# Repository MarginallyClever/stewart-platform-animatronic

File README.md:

# stewart-platform-animatronic

https://www.instagram.com/p/BleN0-bjPU8/

These are the printed parts, PCB design files, and laser cutting plans for miniature stewart platforms used in animatronics.

There are four in the instagram link above.  To make ONE of these platforms you will need

6x M3 rod 10cm long
12x M3x10 screws (can be M3x15)
18x M3x15 screws
3x 3d printed lower gimbal limit
6x 3d printed servo horn 
6x 3d printed servo mount
1x 3d printed top
1x laser cut floor A
1x laser cut floor B

For the handle you'll need 3x M3x15 screws.

To fit the servo into the servo mount I unscrewed the back so the wire would bend down and out of the way.  This is convenient on the input side where I also removed one gear AND unsoldered the white wire and resoldered it to the potentiometer.

The potentiometer returns a value between ~110 and ~520 (of a possible 0-1023).  In the code I adjusted the floor and ceiling values to get the full range of motion out of the servos.

To attach the arms to the input servos, I opened the serial window and turned the servo until it was in middle position, then attached the arm horizontally.  The output servos could then be attached to match.  If there's a better way to do this, please let me know.

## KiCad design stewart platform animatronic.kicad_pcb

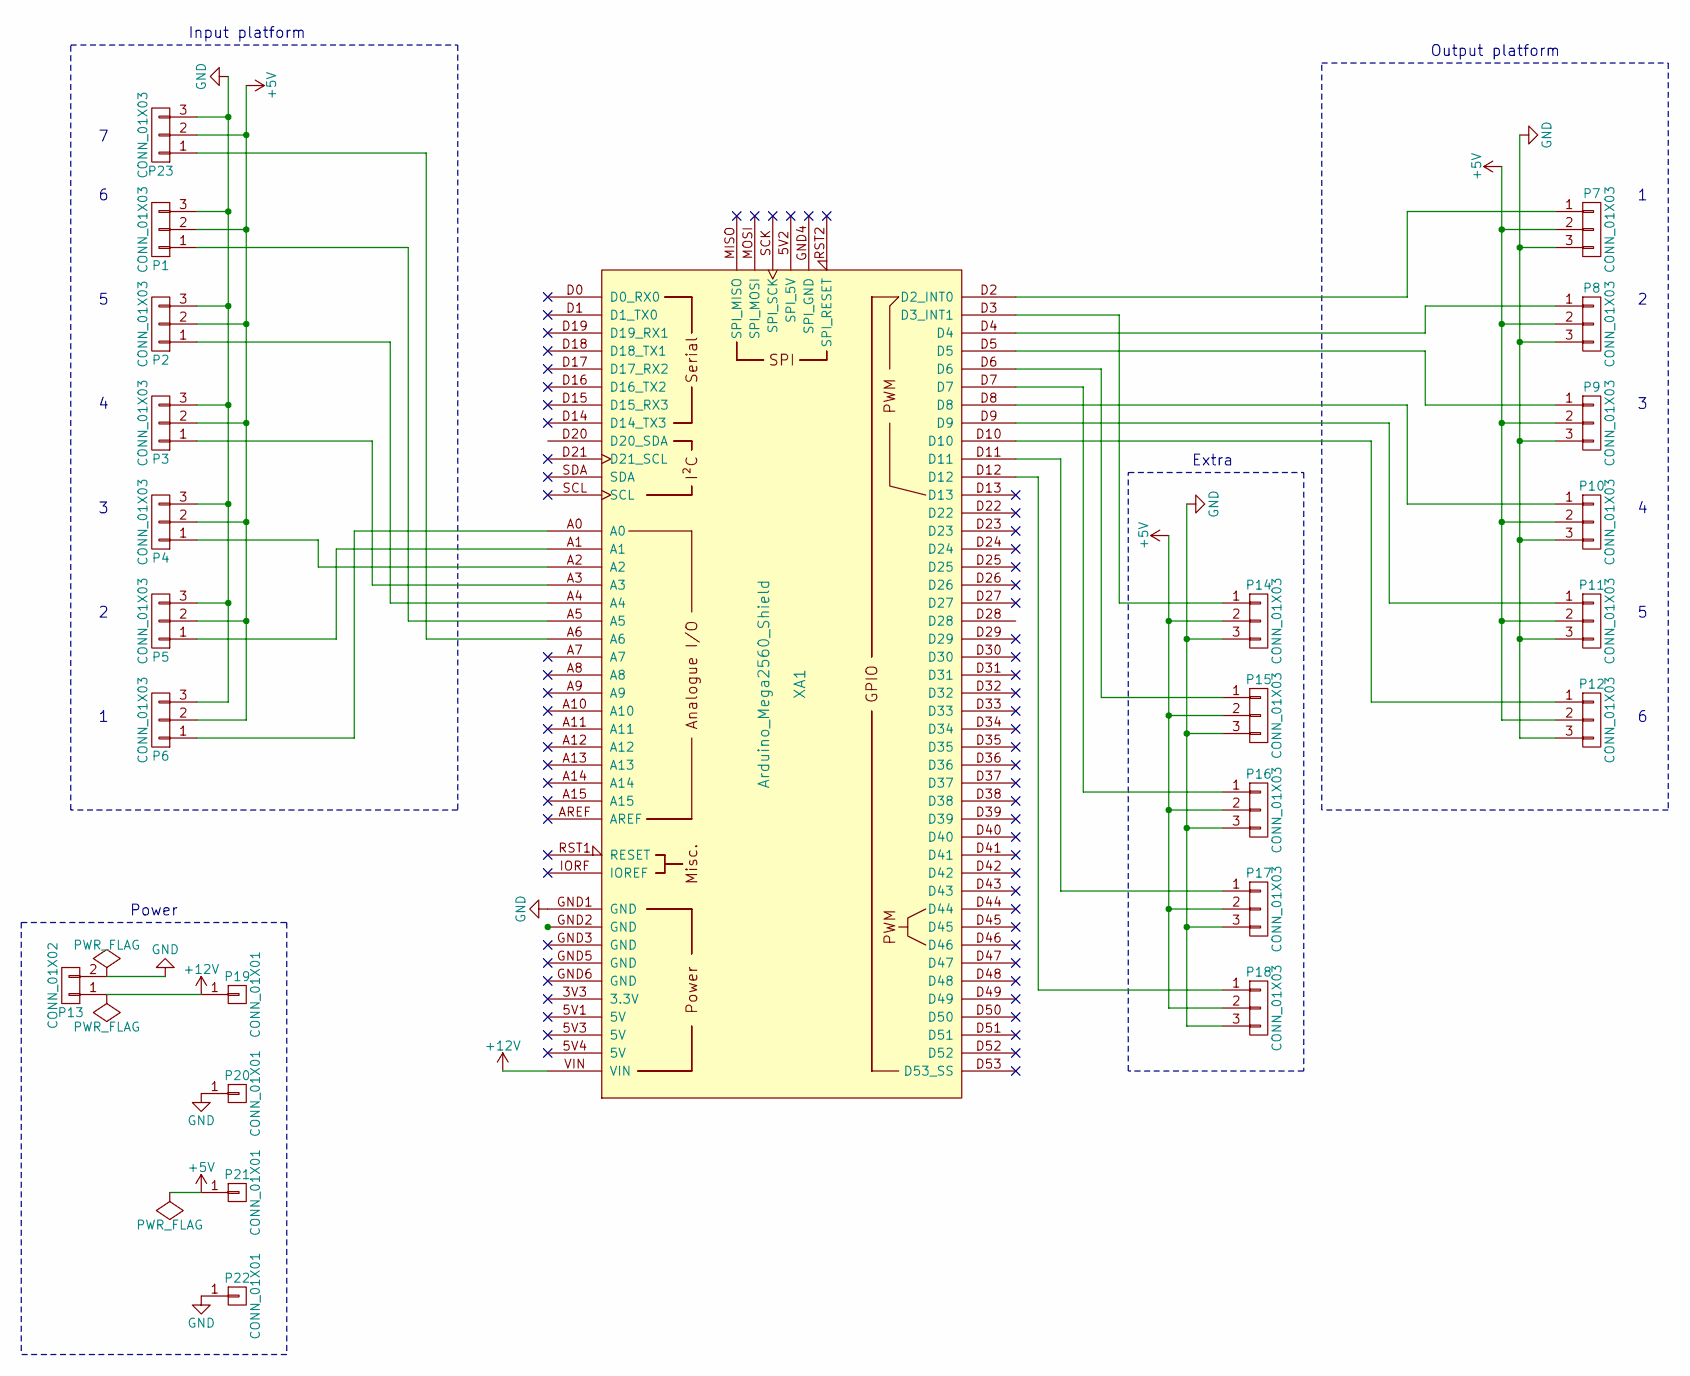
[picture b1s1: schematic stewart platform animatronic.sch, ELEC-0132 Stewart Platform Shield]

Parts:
P1, P2, P3, P4, P5, P6, P7, P8, P9, P10, P11, P12, P14, P15, P16, P17, P18, P23: CONN_01X03; Socket_Strip_Straight_1x03_Pitch2.54mm
P13: CONN_01X02; TerminalBlock_bornier-2_P5.08mm
P19, P20, P21, P22: CONN_01X01; Socket_Strip_Straight_1x01_Pitch2.54mm
XA1: Arduino_Mega2560_Shield

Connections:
+5V: P1.2, P2.2, P3.2, P4.2, P5.2, P6.2, P7.2, P8.2, P9.2, P10.2, P11.2, P12.2, P14.2, P15.2, P16.2, P17.2, P18.2, P21.1, P23.2
+12V: P13.1, P19.1, XA1.VIN
GND: P1.3, P2.3, P3.3, P4.3, P5.3, P6.3, P7.3, P8.3, P9.3, P10.3, P11.3, P12.3, P13.2, P14.3, P15.3, P16.3, P17.3, P18.3, P20.1, P22.1, P23.3, XA1.GND1 (GND)
unnamed: P1.1, XA1.A5
unnamed: P2.1, XA1.A4
unnamed: P3.1, XA1.A3
unnamed: P4.1, XA1.A2
unnamed: P5.1, XA1.A1
unnamed: P6.1, XA1.A0
unnamed: P7.1, XA1.D2 (D2_INT0)
unnamed: P8.1, XA1.D4
unnamed: P9.1, XA1.D5
unnamed: P10.1, XA1.D8
unnamed: P11.1, XA1.D9
unnamed: P12.1, XA1.D10
unnamed: P14.1, XA1.D3 (D3_INT1)
unnamed: P15.1, XA1.D6
unnamed: P16.1, XA1.D7
unnamed: P17.1, XA1.D11
unnamed: P18.1, XA1.D12
unnamed: P23.1, XA1.A6

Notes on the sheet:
Input platform
Output platform
Power
Extra
1 2 3 4 5 6
6 5 4 3 2 1

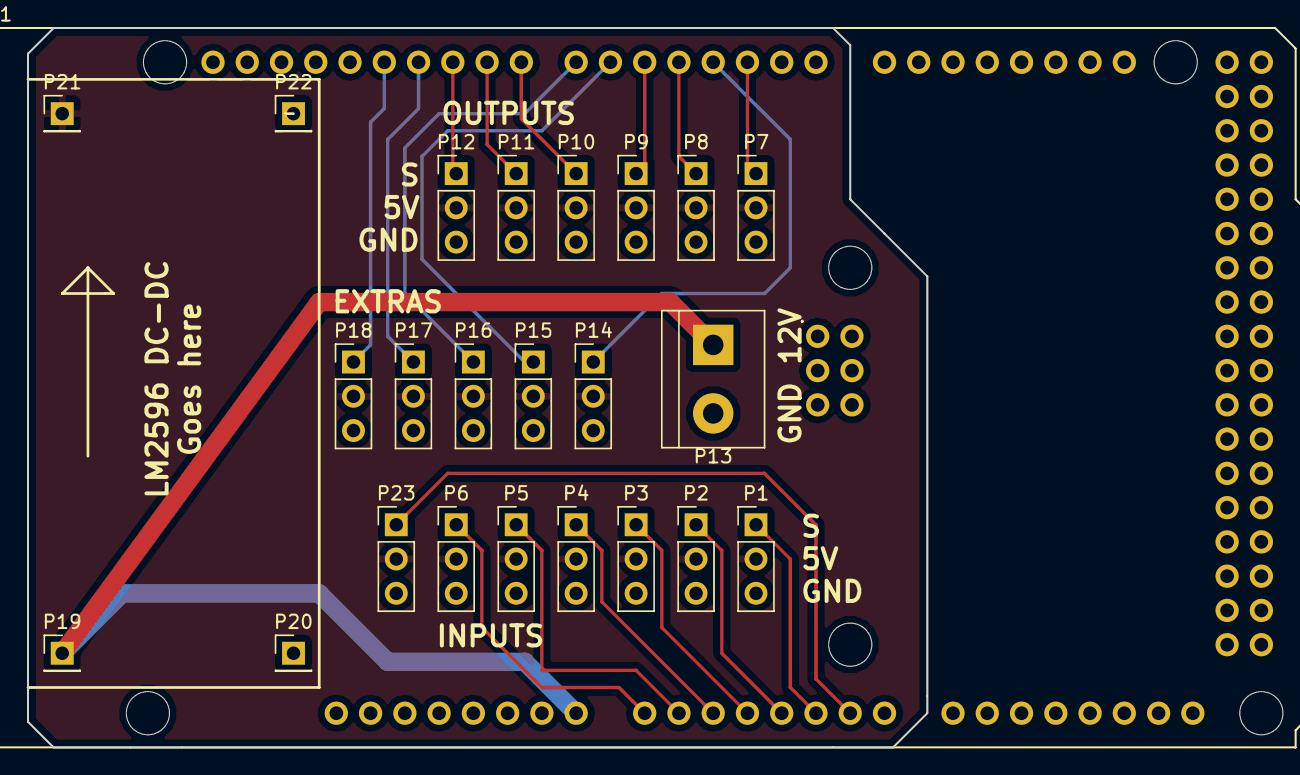
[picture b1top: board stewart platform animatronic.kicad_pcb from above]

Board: 2 copper layers, 66.7 x 53.3 mm, 24 parts (0 on the bottom side), 21 nets.

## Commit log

2018-07-30 updated README, laser cut plans
2018-07-30 mega2560 version
2018-08-05 updated PCB for MEGA
    for MEGA design
2019-12-05 updated kicad version
